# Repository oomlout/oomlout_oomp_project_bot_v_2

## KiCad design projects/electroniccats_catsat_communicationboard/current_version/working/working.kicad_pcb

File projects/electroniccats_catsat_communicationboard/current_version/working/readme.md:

# catsat
 
## summary 
* id: electroniccats_catsat_communicationboard
* user: electroniccats
* name: catsat
* board: communicationboard
* repo: https://github.com/ElectronicCats/CatSat
* src_file_repo_kicad_pcb: CommunicationBoard/CommunicationBoard.kicad_pcb
* src_file_repo_kicad_pcb_link: https://github.com/ElectronicCats/CatSat/tree/master/CommunicationBoard/CommunicationBoard.kicad_pcb

* src_file_repo_sch: CommunicationBoard/CommunicationBoard.sch
* src_file_repo_sch_link: https://github.com/ElectronicCats/CatSat/tree/master/CommunicationBoard/CommunicationBoard.sch
* full details link: https://github.com/oomlout/oomlout_oomp_project_bot_v_2/tree/main/projects/electroniccats_catsat_communicationboard/current_version/working

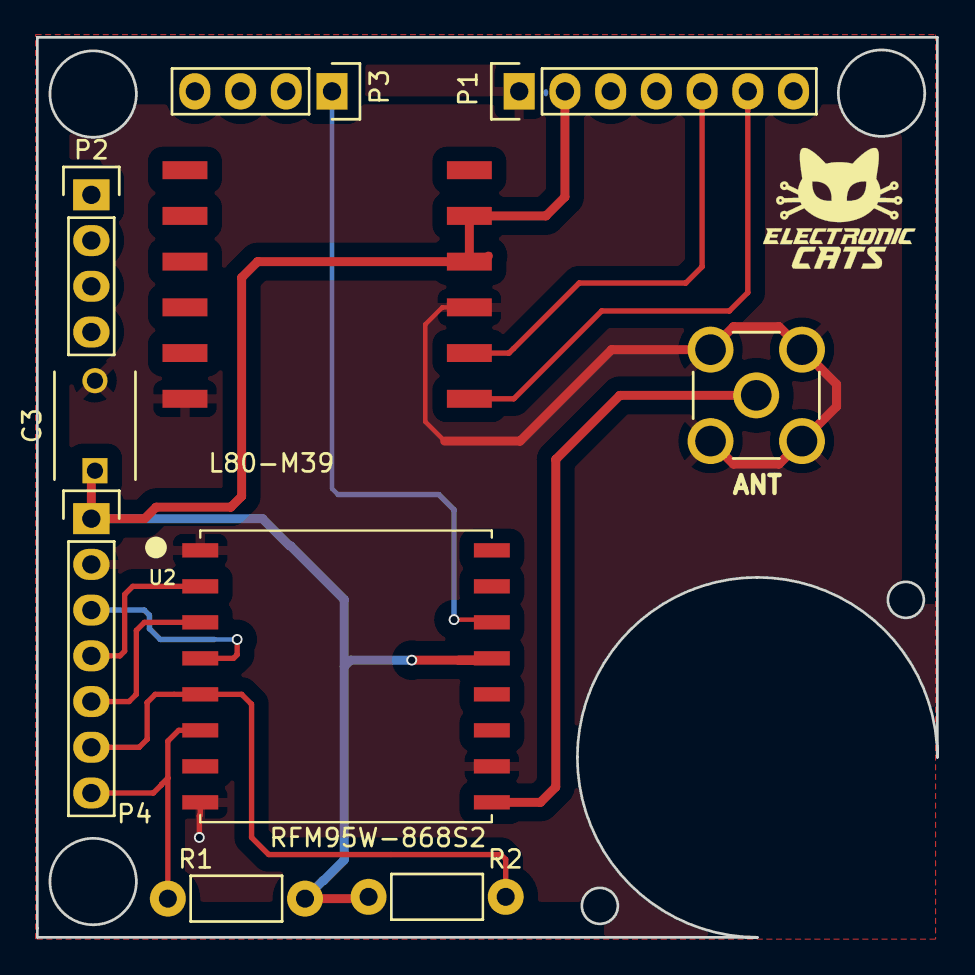
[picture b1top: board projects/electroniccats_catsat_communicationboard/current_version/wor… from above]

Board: 2 copper layers, 50.0 x 50.0 mm, 10 parts (0 on the bottom side), 11 nets.

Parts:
A1: ANT; AMPHENOL_901-144
C3: C; C_Disc_D6_P5
MODULE1: L80-M39; L80
P1, P4: CONN_01X07; Pin_Header_Straight_1x07
P2, P3: CONN_01X04; Pin_Header_Straight_1x04
R1, R2: R; Resistor_Horizontal_RM7mm
U2: RFM95W-868S2; RFM

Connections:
+BATT: C3.1, MODULE1.4, MODULE1.5, P1.2, P4.1, R1.1, R2.1, U2.13
GND: A1.2, A1.3, A1.4, A1.5, C3.2, MODULE1.3, MODULE1.12, P1.1, P4.2, U2.1, U2.8, U2.10
INT0: P3.1, U2.14
MISO: P4.4, U2.2
MOSI: P4.5, U2.3
NSS: P4.6, R2.2, U2.5
unnamed: A1.1, U2.9
RST: P4.7, R1.2, U2.6
SCK: P4.3, U2.4
S_RX: MODULE1.2, P1.5
S_TX: MODULE1.1, P1.6

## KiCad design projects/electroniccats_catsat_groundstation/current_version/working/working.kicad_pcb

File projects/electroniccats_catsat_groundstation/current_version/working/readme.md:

# catsat
 
## summary 
* id: electroniccats_catsat_groundstation
* user: electroniccats
* name: catsat
* board: groundstation
* repo: https://github.com/ElectronicCats/CatSat
* src_file_repo_kicad_pcb: GroundStation/GroundStation.kicad_pcb
* src_file_repo_kicad_pcb_link: https://github.com/ElectronicCats/CatSat/tree/master/GroundStation/GroundStation.kicad_pcb

* src_file_repo_sch: GroundStation/GroundStation.sch
* src_file_repo_sch_link: https://github.com/ElectronicCats/CatSat/tree/master/GroundStation/GroundStation.sch
* full details link: https://github.com/oomlout/oomlout_oomp_project_bot_v_2/tree/main/projects/electroniccats_catsat_groundstation/current_version/working

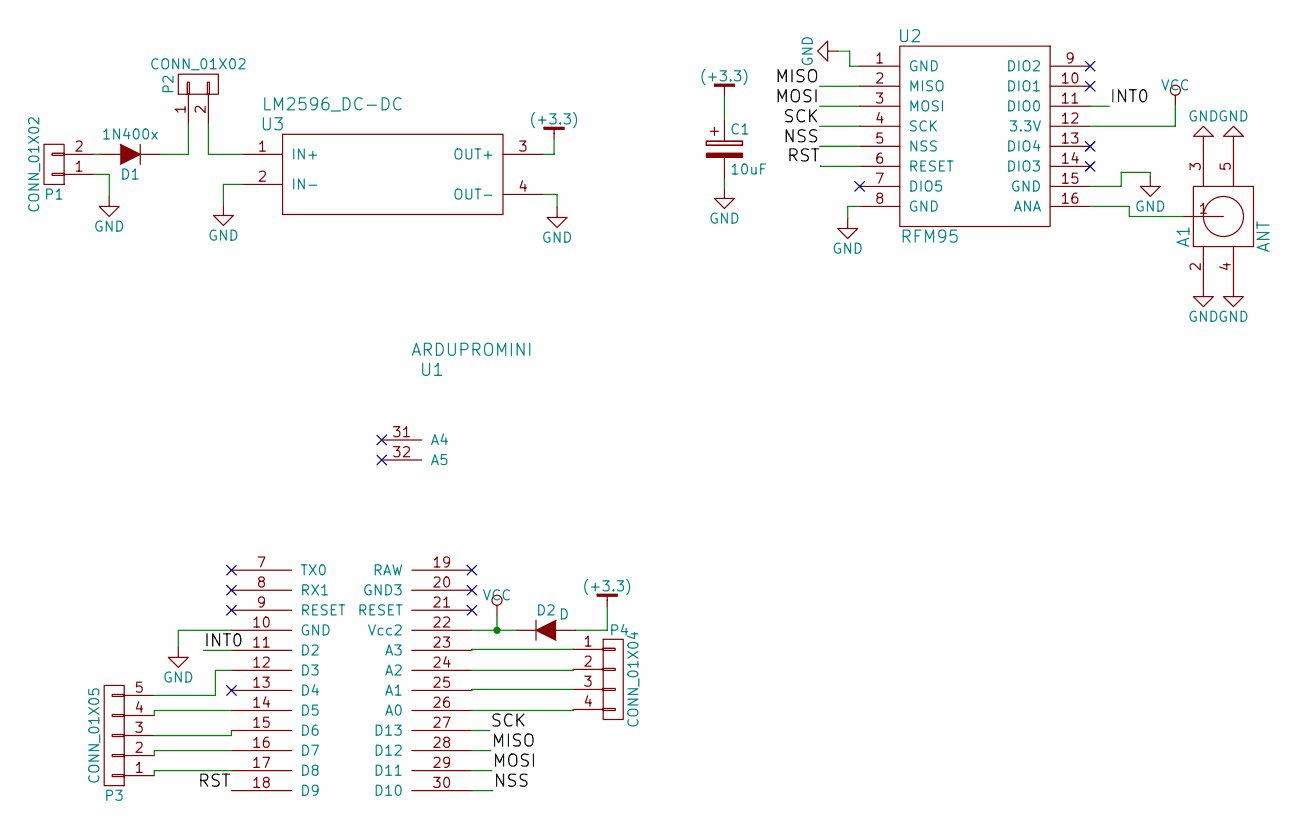
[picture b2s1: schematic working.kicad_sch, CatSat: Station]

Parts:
A1: ANT; AMPHENOL_901-144
C1: 10uF; C_Radial_D5_L6_P2.5
D1: 1N400x; Diode_DO-41_SOD81_Horizontal_RM10
D2: D; Diode_DO-41_SOD81_Horizontal_RM10
P1: CONN_01X02; bornier2
P2: CONN_01X02; Pin_Header_Straight_1x02
P3: CONN_01X05
P4: CONN_01X04
U1: ARDUPROMINI; arduinoMiniPro2
U2: RFM95; RFM
U3: LM2596_DC-DC; LM2596DC-DC

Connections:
(+3.3): C1.1, D2.2 (A), U3.3 (OUT+)
/INT0: U1.11 (D2), U2.11 (DIO0)
/MISO: U1.28 (D12), U2.2 (MISO)
/MOSI: U1.29 (D11), U2.3 (MOSI)
/NSS: U1.30 (D10), U2.5 (NSS)
/RST: U1.18 (D9), U2.6 (RESET)
/SCK: U1.27 (D13), U2.4 (SCK)
GND: A1.2, A1.3, A1.4, A1.5, C1.2, P1.1, U1.10 (GND), U2.1 (GND), U2.8 (GND), U2.15 (GND), U3.2 (IN-), U3.4 (OUT-)
unnamed: A1.1, U2.16 (ANA)
unnamed: D1.1 (K), P2.1
unnamed: D1.2 (A), P1.2
unnamed: P2.2, U3.1 (IN+)
unnamed: P3.1, U1.17 (D8)
unnamed: P3.2, U1.16 (D7)
unnamed: P3.3, U1.15 (D6)
unnamed: P3.4, U1.14 (D5)
unnamed: P3.5, U1.12 (D3)
unnamed: P4.1, U1.23 (A3)
unnamed: P4.2, U1.24 (A2)
unnamed: P4.3, U1.25 (A1)
unnamed: P4.4, U1.26 (A0)
VCC: D2.1 (K), U1.22 (Vcc2), U2.12 (3.3V)

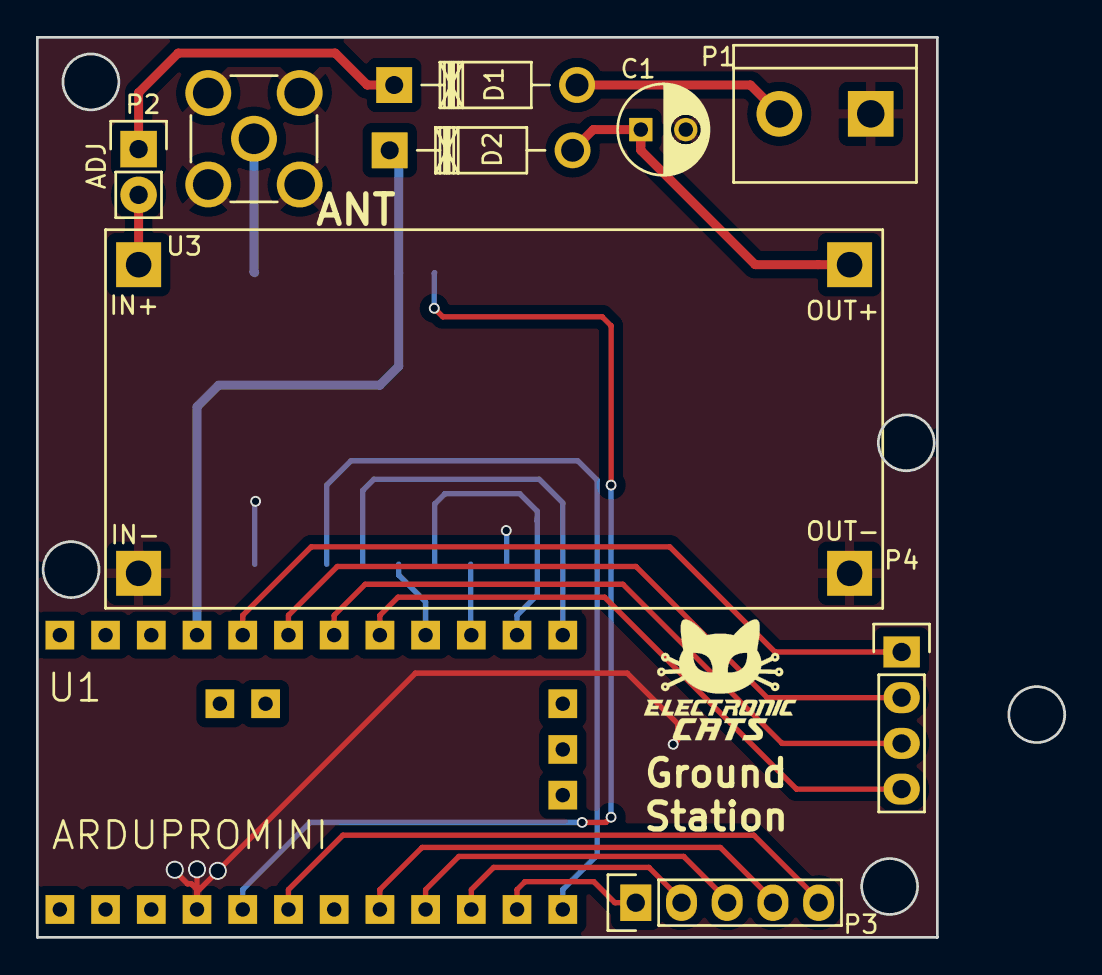
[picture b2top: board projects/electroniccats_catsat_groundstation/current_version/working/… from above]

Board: 2 copper layers, 50.0 x 50.0 mm, 11 parts (1 on the bottom side), 22 nets.

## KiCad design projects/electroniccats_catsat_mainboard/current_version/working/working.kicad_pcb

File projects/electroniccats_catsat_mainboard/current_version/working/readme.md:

# catsat
 
## summary 
* id: electroniccats_catsat_mainboard
* user: electroniccats
* name: catsat
* board: mainboard
* repo: https://github.com/ElectronicCats/CatSat
* src_file_repo_kicad_pcb: MainBoard/MainBoard.kicad_pcb
* src_file_repo_kicad_pcb_link: https://github.com/ElectronicCats/CatSat/tree/master/MainBoard/MainBoard.kicad_pcb

* src_file_repo_sch: MainBoard/MainBoard.sch
* src_file_repo_sch_link: https://github.com/ElectronicCats/CatSat/tree/master/MainBoard/MainBoard.sch
* full details link: https://github.com/oomlout/oomlout_oomp_project_bot_v_2/tree/main/projects/electroniccats_catsat_mainboard/current_version/working

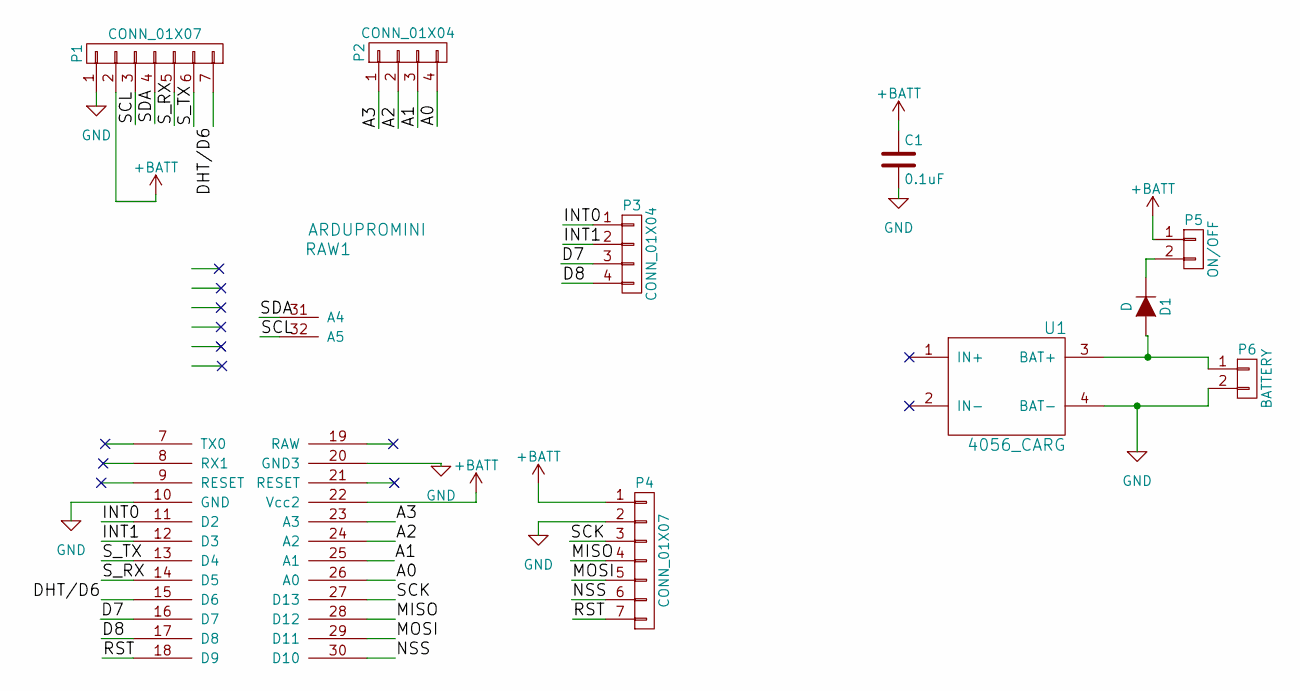
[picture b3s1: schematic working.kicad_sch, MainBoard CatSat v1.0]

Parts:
C1: 0.1uF; C_Disc_D6_P5
D1: D; Diode_DO-41_SOD81_Horizontal_RM10
P1, P4: CONN_01X07; Pin_Header_Straight_1x07
P2, P3: CONN_01X04; Pin_Header_Straight_1x04
P5: ON/OFF; Pin_Header_Angled_1x02
P6: BATTERY; Pin_Header_Straight_1x02
RAW1: ARDUPROMINI; arduinoMiniPro
U1: 4056_CARG; 4056_lipoCharg

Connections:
+BATT: C1.1, P1.2, P4.1, P5.1, RAW1.22 (Vcc2)
/A0: P2.4, RAW1.26 (A0)
/A1: P2.3, RAW1.25 (A1)
/A2: P2.2, RAW1.24 (A2)
/A3: P2.1, RAW1.23 (A3)
/D7: P3.3, RAW1.16 (D7)
/D8: P3.4, RAW1.17 (D8)
/DHT/D6: P1.7, RAW1.15 (D6)
/INT0: P3.1, RAW1.11 (D2)
/INT1: P3.2, RAW1.12 (D3)
/MISO: P4.4, RAW1.28 (D12)
/MOSI: P4.5, RAW1.29 (D11)
/NSS: P4.6, RAW1.30 (D10)
/RST: P4.7, RAW1.18 (D9)
/SCK: P4.3, RAW1.27 (D13)
/SCL: P1.3, RAW1.32 (A5)
/SDA: P1.4, RAW1.31 (A4)
/S_RX: P1.5, RAW1.14 (D5)
/S_TX: P1.6, RAW1.13 (D4)
GND: C1.2, P1.1, P4.2, P6.2, RAW1.10 (GND), RAW1.20 (GND3), U1.4 (BAT-)
unnamed: D1.1 (K), P5.2
unnamed: D1.2 (A), P6.1, U1.3 (BAT+)

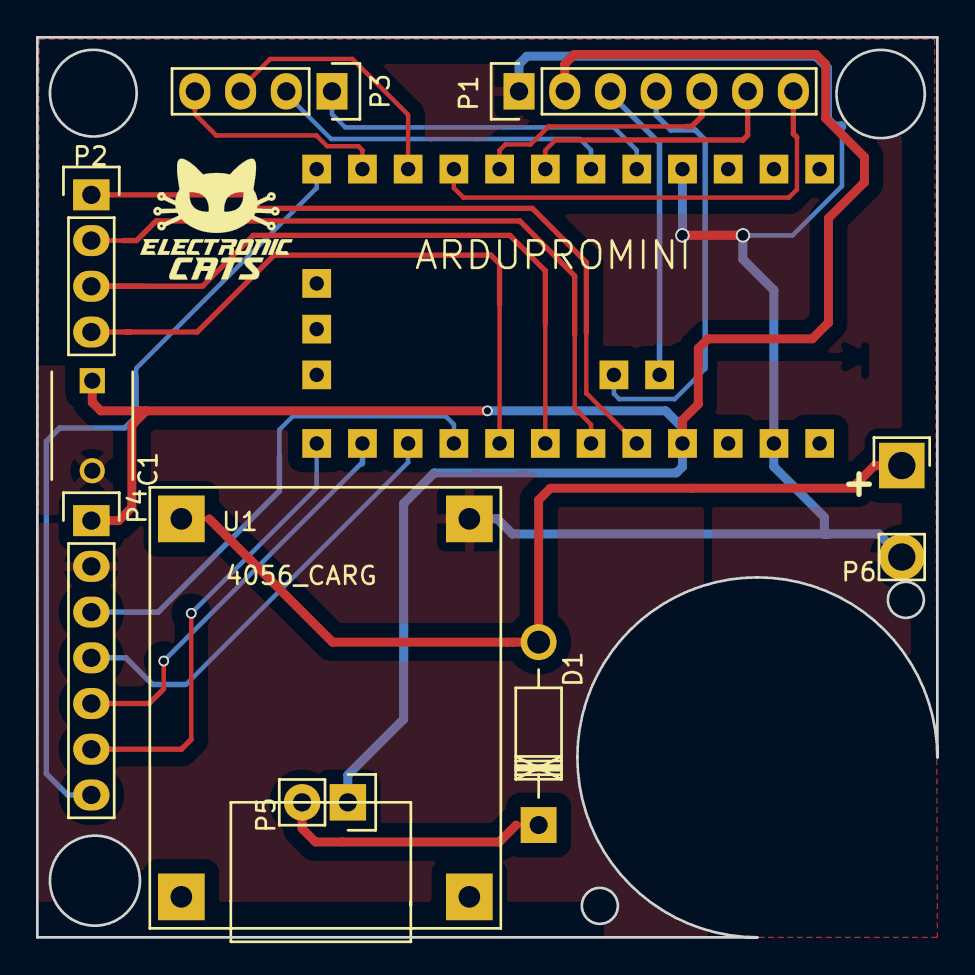
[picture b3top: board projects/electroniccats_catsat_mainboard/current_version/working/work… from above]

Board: 2 copper layers, 50.0 x 50.0 mm, 10 parts (0 on the bottom side), 22 nets.

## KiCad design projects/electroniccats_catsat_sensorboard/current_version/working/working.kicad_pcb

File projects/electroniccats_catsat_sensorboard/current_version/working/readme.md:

# catsat
 
## summary 
* id: electroniccats_catsat_sensorboard
* user: electroniccats
* name: catsat
* board: sensorboard
* repo: https://github.com/ElectronicCats/CatSat
* src_file_repo_kicad_pcb: SensorBoard/SensorBoard.kicad_pcb
* src_file_repo_kicad_pcb_link: https://github.com/ElectronicCats/CatSat/tree/master/SensorBoard/SensorBoard.kicad_pcb

* src_file_repo_sch: SensorBoard/SensorBoard.sch
* src_file_repo_sch_link: https://github.com/ElectronicCats/CatSat/tree/master/SensorBoard/SensorBoard.sch
* full details link: https://github.com/oomlout/oomlout_oomp_project_bot_v_2/tree/main/projects/electroniccats_catsat_sensorboard/current_version/working

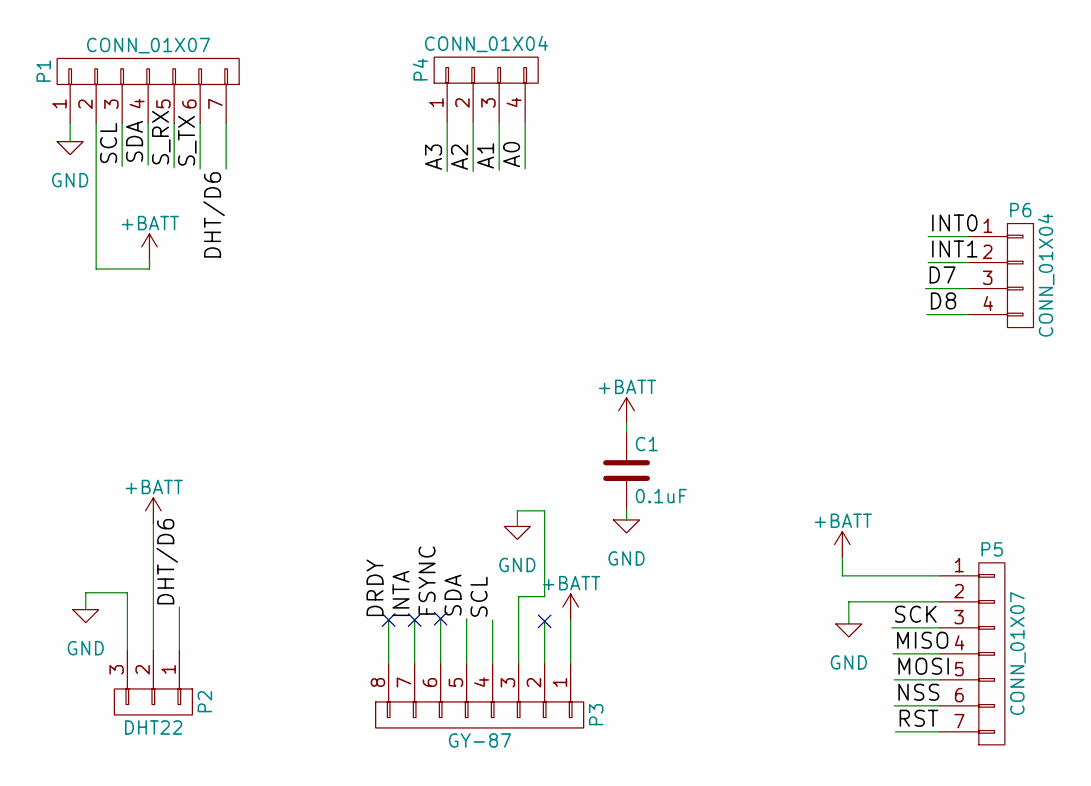
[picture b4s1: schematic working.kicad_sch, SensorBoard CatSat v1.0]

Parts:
C1: 0.1uF; C_Disc_D6_P5
P1, P5: CONN_01X07; Pin_Header_Straight_1x07
P2: DHT22; Pin_Header_Straight_1x03
P3: GY-87; Pin_Header_Straight_1x08
P4, P6: CONN_01X04; Pin_Header_Straight_1x04

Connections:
+BATT: C1.1, P1.2, P2.2, P3.1, P5.1
/A0: P4.4
/A1: P4.3
/A2: P4.2
/A3: P4.1
/D7: P6.3
/D8: P6.4
/DHT/D6: P1.7, P2.1
/DRDY: P3.8
/FSYNC: P3.6
/INT0: P6.1
/INT1: P6.2
/INTA: P3.7
/MISO: P5.4
/MOSI: P5.5
/NSS: P5.6
/RST: P5.7
/SCK: P5.3
/SCL: P1.3, P3.4
/SDA: P1.4, P3.5
/S_RX: P1.5
/S_TX: P1.6
GND: C1.2, P1.1, P2.3, P3.3, P5.2

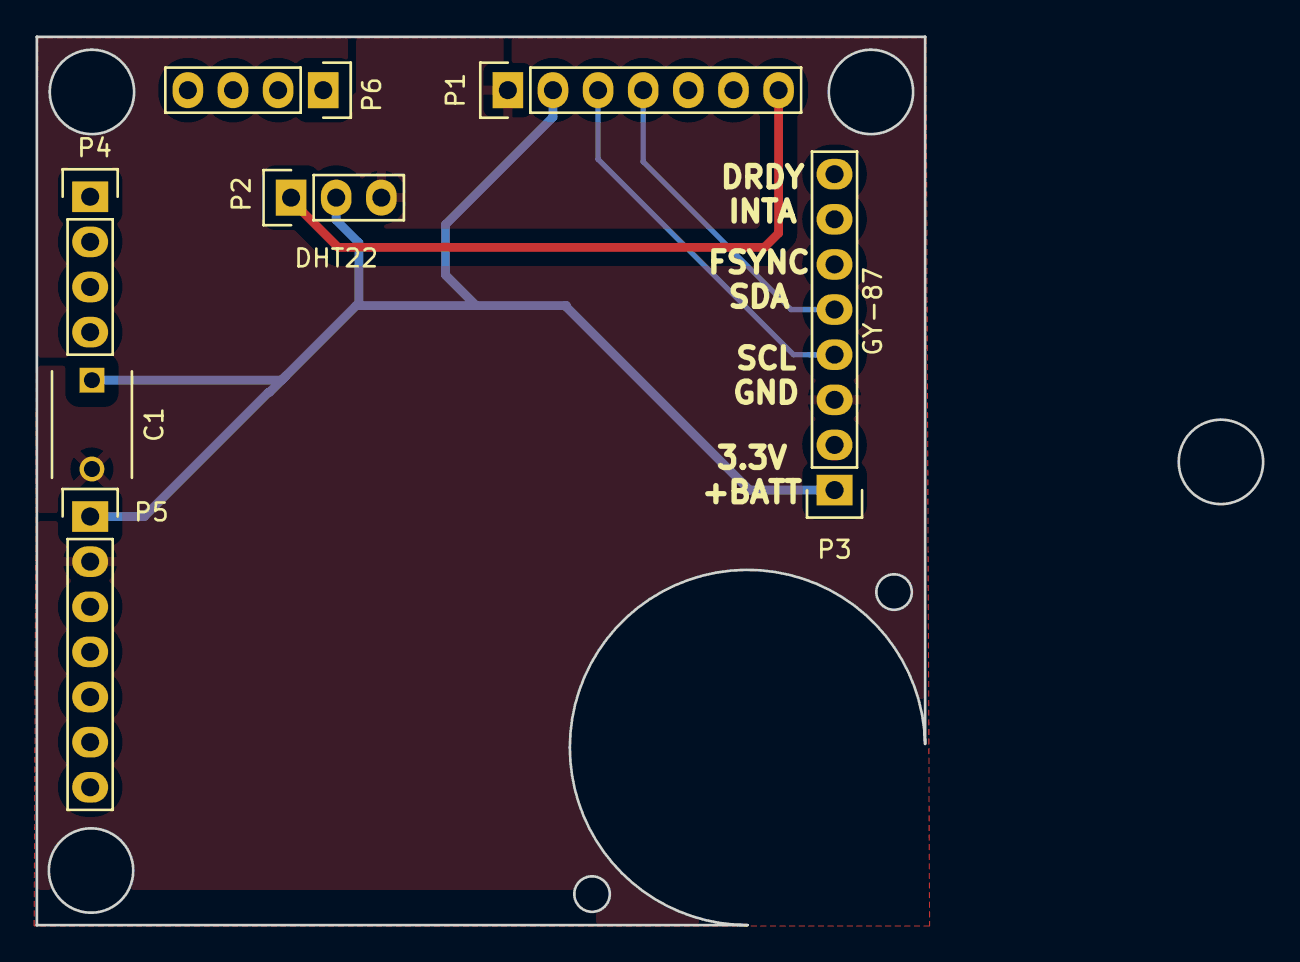
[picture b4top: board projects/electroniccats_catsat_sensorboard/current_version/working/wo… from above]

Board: 2 copper layers, 50.0 x 50.0 mm, 7 parts (0 on the bottom side), 5 nets.

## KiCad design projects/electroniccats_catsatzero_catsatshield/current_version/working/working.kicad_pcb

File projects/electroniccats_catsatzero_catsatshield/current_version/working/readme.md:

# catsatzero
 
## summary 
* id: electroniccats_catsatzero_catsatshield
* user: electroniccats
* name: catsatzero
* board: catsatshield
* repo: https://github.com/ElectronicCats/CatSatZero
* src_file_repo_kicad_pcb: CatSatShield/CaTSatShield.kicad_pcb
* src_file_repo_kicad_pcb_link: https://github.com/ElectronicCats/CatSatZero/tree/master/CatSatShield/CaTSatShield.kicad_pcb

* src_file_repo_sch: CatSatShield/CaTSatShield.sch
* src_file_repo_sch_link: https://github.com/ElectronicCats/CatSatZero/tree/master/CatSatShield/CaTSatShield.sch
* full details link: https://github.com/oomlout/oomlout_oomp_project_bot_v_2/tree/main/projects/electroniccats_catsatzero_catsatshield/current_version/working

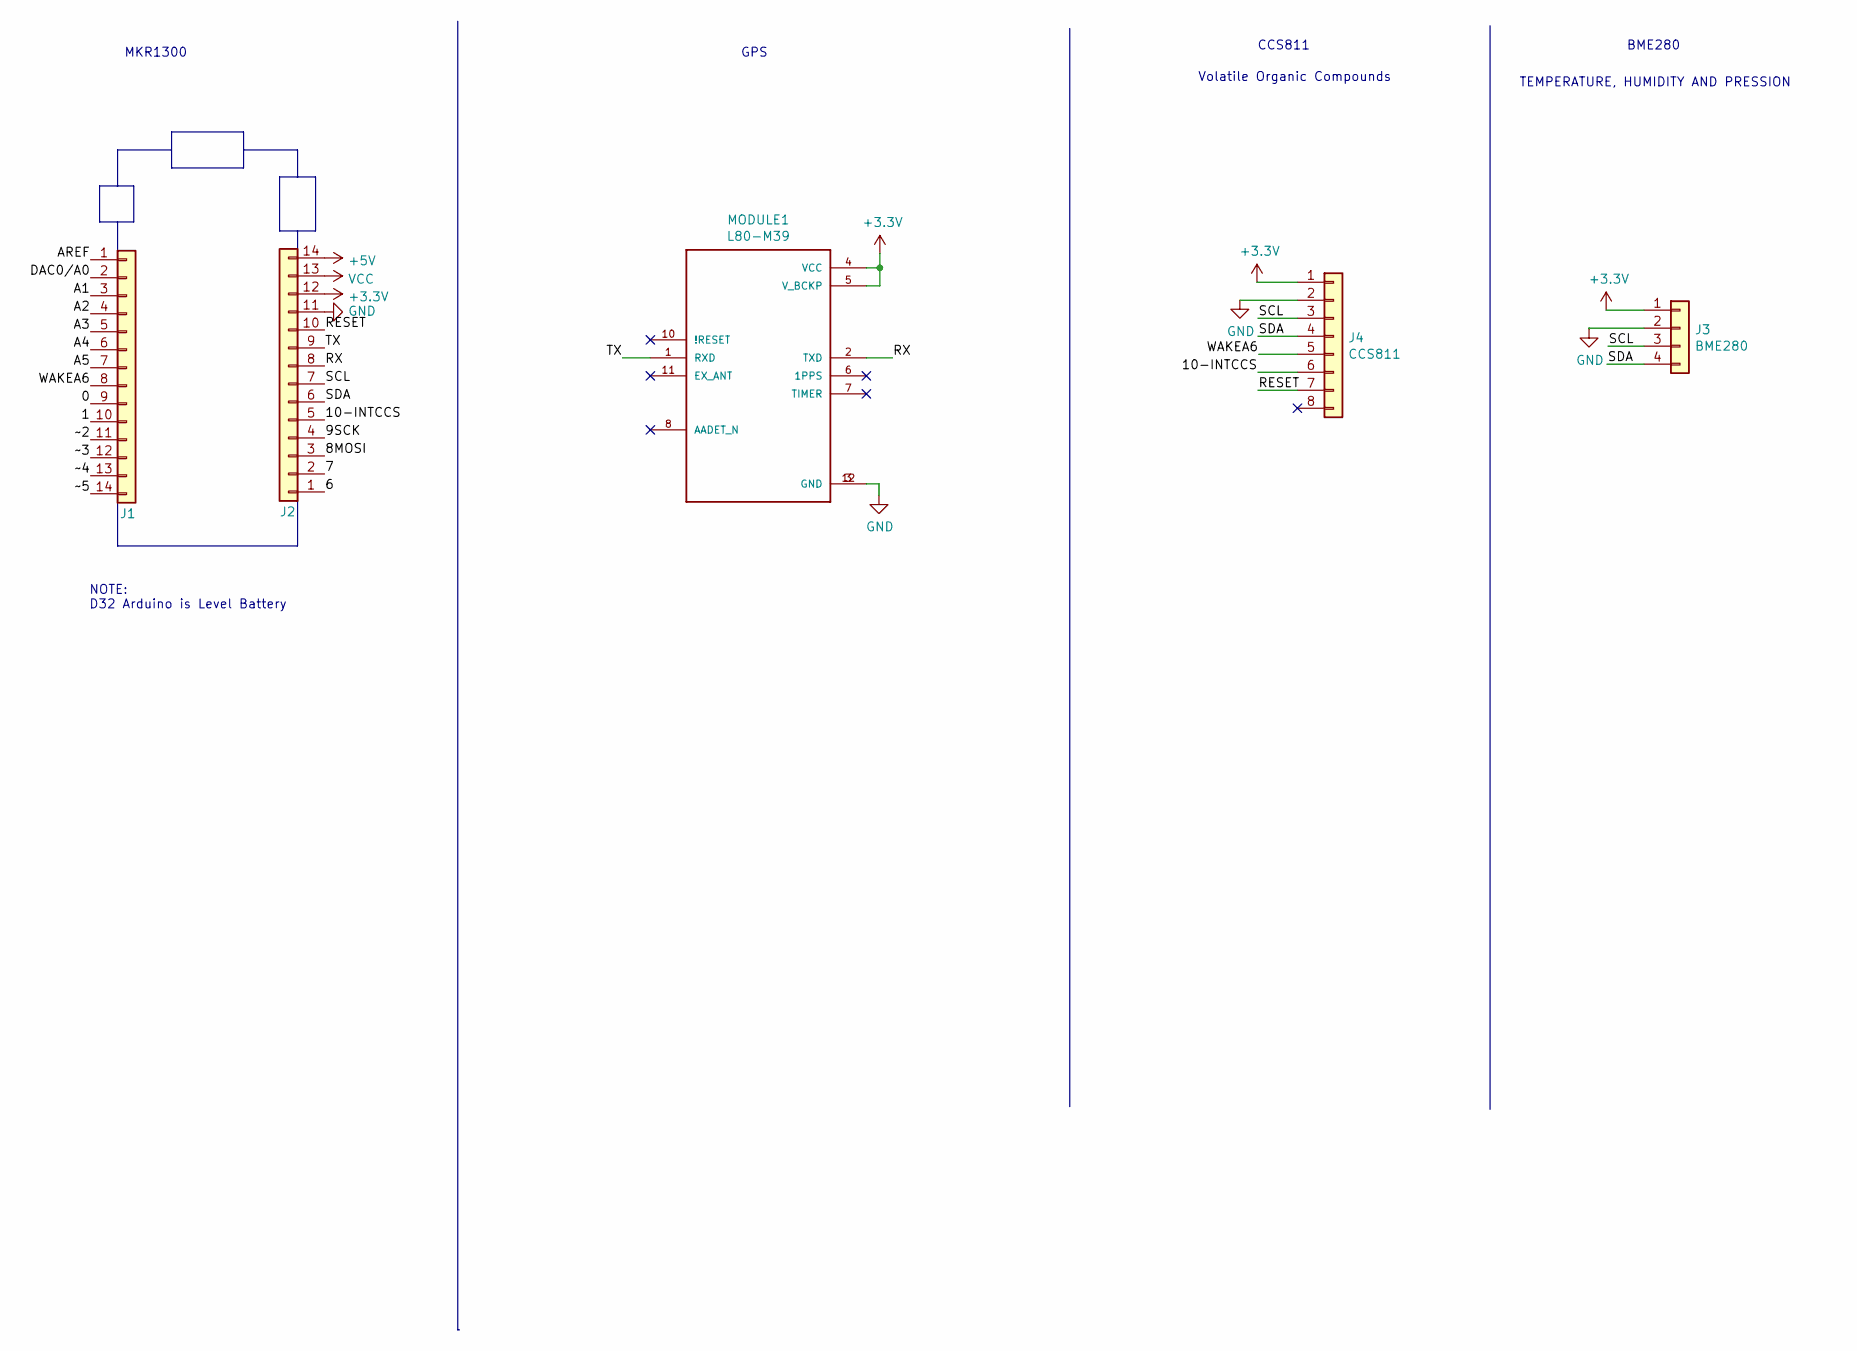
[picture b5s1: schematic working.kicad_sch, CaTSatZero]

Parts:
J1, J2: 61301411121
J3: BME280; PinSocket_1x04_P2.54mm_Vertical
J4: CCS811; Pin_Header_Straight_1x07_Pitch2.54mm
MODULE1: L80-M39; QUECTEL_L80-M39

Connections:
+3V3: J2.12, J3.1, J4.1, MODULE1.4 (VCC), MODULE1.5 (V_BCKP)
+5V: J2.14
/0: J1.9
/1: J1.10
/6: J2.1
/7: J2.2
/8MOSI: J2.3
/9SCK: J2.4
/10-INTCCS: J2.5, J4.6
/A1: J1.3
/A2: J1.4
/A3: J1.5
/A4: J1.6
/A5: J1.7
/AREF: J1.1
/DAC0/A0: J1.2
/RESET: J2.10, J4.7
/RX: J2.8, MODULE1.2 (TXD)
/SCL: J2.7, J3.3, J4.3
/SDA: J2.6, J3.4, J4.4
/TX: J2.9, MODULE1.1 (RXD)
/WAKEA6: J1.8, J4.5
/~2: J1.11
/~3: J1.12
/~4: J1.13
/~5: J1.14
GND: J2.11, J3.2, J4.2, MODULE1.3 (GND), MODULE1.12 (GND)
VCC: J2.13

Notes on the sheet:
TEMPERATURE, HUMIDITY AND PRESSION
Volatile Organic Compounds
NOTE: D32 Arduino is Level Battery
BME280
GPS
CCS811
MKR1300

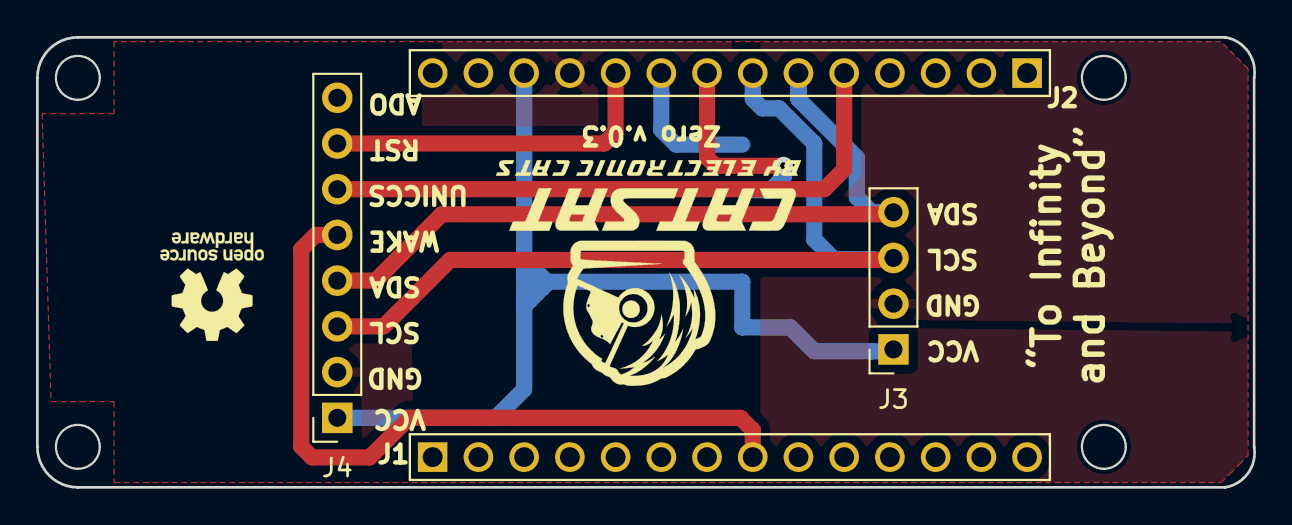
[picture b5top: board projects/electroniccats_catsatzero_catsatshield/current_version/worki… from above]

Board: 2 copper layers, 67.6 x 25.0 mm, 14 parts (1 on the bottom side), 9 nets.

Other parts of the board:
@HOLE0, @HOLE1, @HOLE2, @HOLE3: (no value)
FRAME1: Page 1; FRAME
U$5, U$6, U$7, U$8: MH_RND_F_2.2MM_NM

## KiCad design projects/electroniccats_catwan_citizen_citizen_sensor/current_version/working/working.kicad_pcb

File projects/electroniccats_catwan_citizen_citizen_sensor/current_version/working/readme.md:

# catwan_citizen
 
## summary 
* id: electroniccats_catwan_citizen_citizen_sensor
* user: electroniccats
* name: catwan_citizen
* board: citizen_sensor
* repo: https://github.com/ElectronicCats/CatWAN_Citizen
* src_file_repo_kicad_pcb: Hardware/citizen_sensor.kicad_pcb
* src_file_repo_kicad_pcb_link: https://github.com/ElectronicCats/CatWAN_Citizen/tree/master/Hardware/citizen_sensor.kicad_pcb
* src_file_repo_kicad_sch: Hardware/citizen_sensor.kicad_sch
* src_file_repo_kicad_sch_link: https://github.com/ElectronicCats/CatWAN_Citizen/tree/master/Hardware/citizen_sensor.kicad_sch

* src_file_repo_sch: Hardware/citizen_sensor.sch
* src_file_repo_sch_link: https://github.com/ElectronicCats/CatWAN_Citizen/tree/master/Hardware/citizen_sensor.sch
* full details link: https://github.com/oomlout/oomlout_oomp_project_bot_v_2/tree/main/projects/electroniccats_catwan_citizen_citizen_sensor/current_version/working

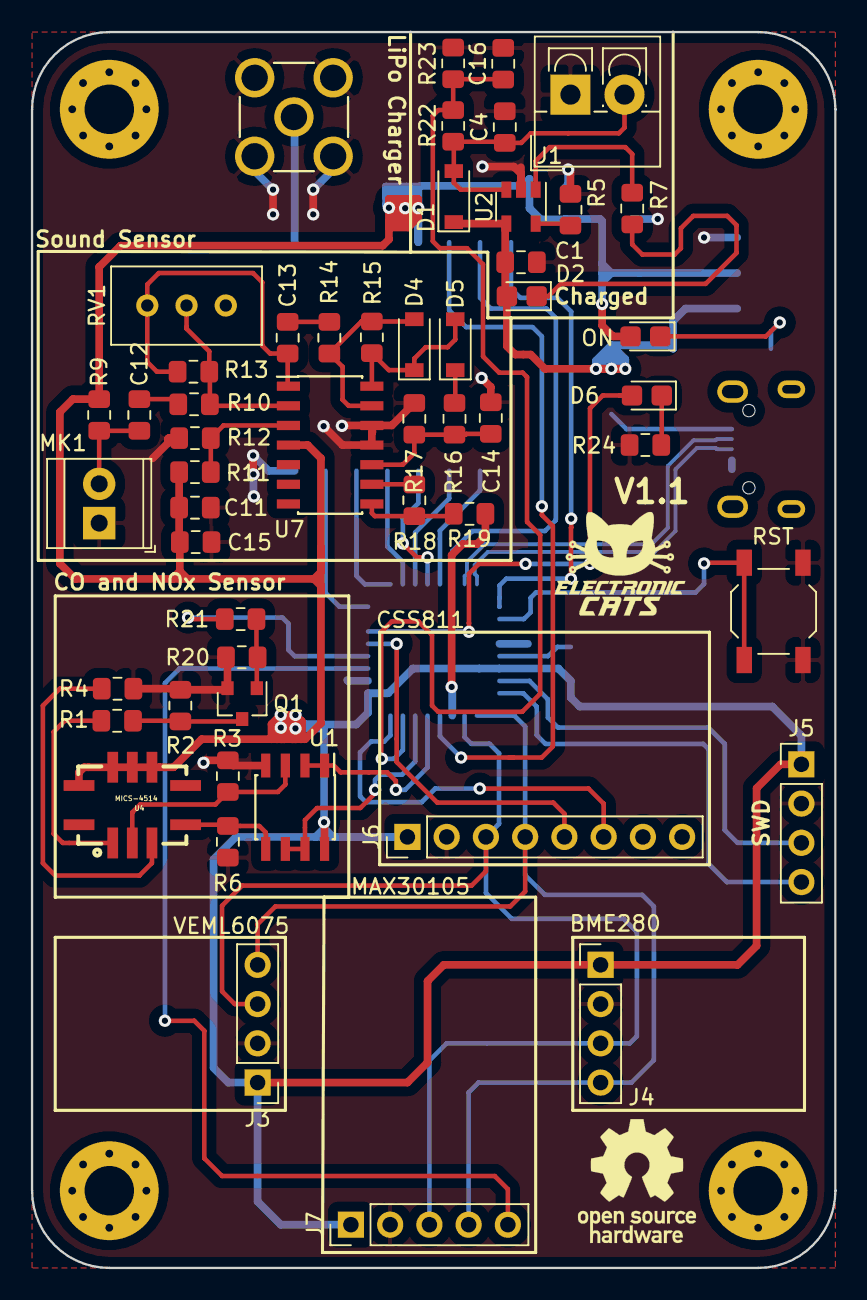
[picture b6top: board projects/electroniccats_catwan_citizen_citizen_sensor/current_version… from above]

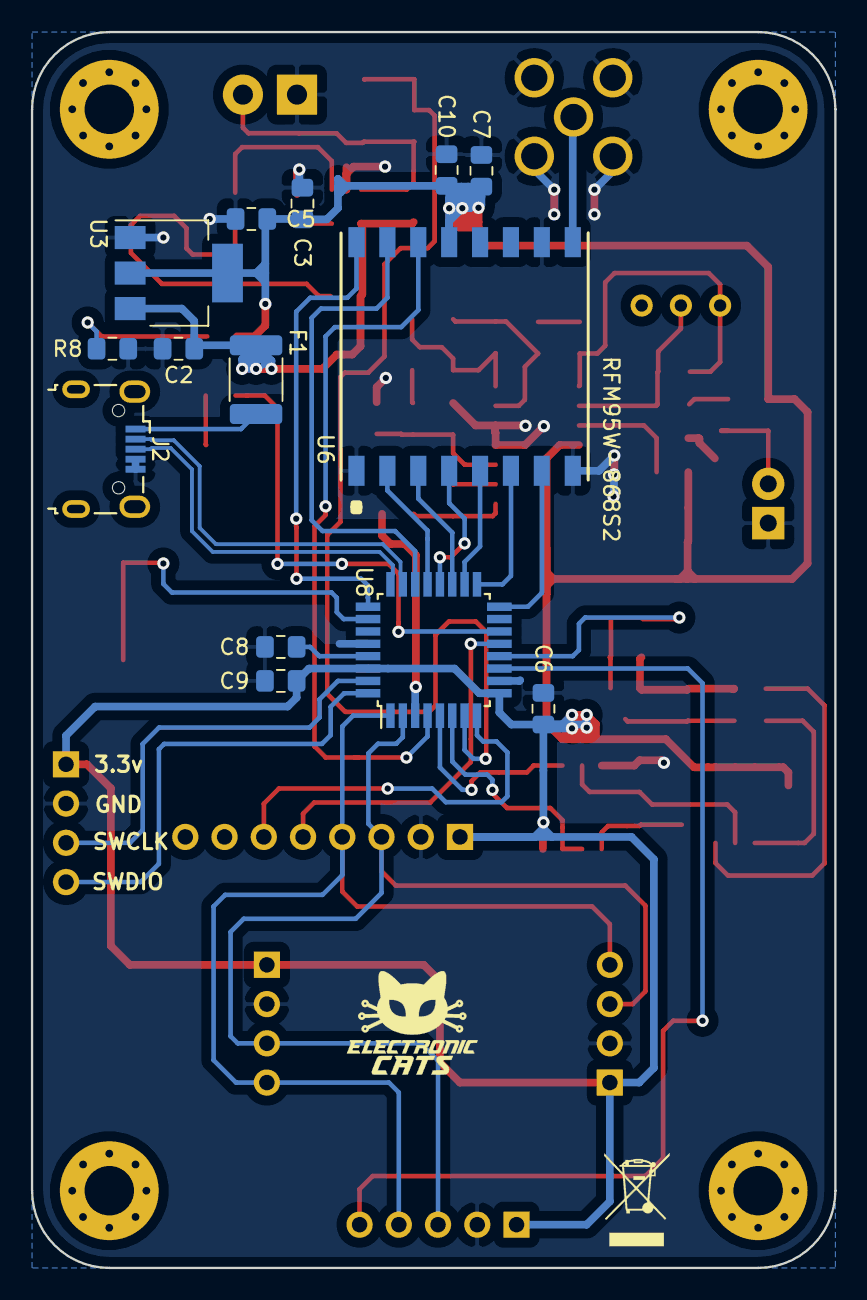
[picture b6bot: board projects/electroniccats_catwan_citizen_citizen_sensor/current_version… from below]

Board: 2 copper layers, 52.0 x 80.0 mm, 66 parts (14 on the bottom side), 55 nets.

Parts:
AE1: Antenna_Shield; AMPHENOL_901-144
C1, C2, C4, C5: 10uf; C_0805_2012Metric_Pad1.15x1.40mm_HandSolder
C3, C6, C7, C9, C15, C16: 0.1uf; C_0805_2012Metric_Pad1.15x1.40mm_HandSolder
C8, C10, C11: 1uf; C_0805_2012Metric_Pad1.15x1.40mm_HandSolder
C12, C14: 10uF; C_0805_2012Metric_Pad1.15x1.40mm_HandSolder
C13: 1uF; C_0805_2012Metric_Pad1.15x1.40mm_HandSolder
D1: D_Schottky; D_SOD-123
D2: CHARGE; LED_0805_2012Metric_Castellated
D3: ON; LED_0805_2012Metric_Castellated
D4, D5: RB751S40T1G; D_SOD-123
D6: Builtin; LED_0805_2012Metric_Castellated
F1: Fuse; Fuse_1812_4532Metric_Pad1.30x3.40mm_HandSolder
J1: BATT; TerminalBlock_4Ucon_1x02_P3.50mm_Vertical
J2: USB_B_Micro; USB_Micro-B_Wuerth_629105150521
J3: VEML6075; PinHeader_1x04_P2.54mm_Vertical
J4: BME280; PinHeader_1x04_P2.54mm_Vertical
J5: PROG; PinHeader_1x04_P2.54mm_Vertical
J6: CSS811; PinHeader_1x08_P2.54mm_Vertical
J7: MAX30105; PinHeader_1x05_P2.54mm_Vertical
MK1: Microphone; TerminalBlock_TE_282834-2_1x02_P2.54mm_Horizontal
Q1: 2N7002; SOT-23
R1, R4: 30; R_0805_2012Metric_Pad1.15x1.40mm_HandSolder
R2: 36; R_0805_2012Metric_Pad1.15x1.40mm_HandSolder
R3: 269; R_0805_2012Metric_Pad1.15x1.40mm_HandSolder
R5: 10k; R_0805_2012Metric_Pad1.15x1.40mm_HandSolder
R6: 47k; R_0805_2012Metric_Pad1.15x1.40mm_HandSolder
R7: 1k; R_0805_2012Metric_Pad1.15x1.40mm_HandSolder
R8, R24: 330; R_0805_2012Metric_Pad1.15x1.40mm_HandSolder
R9: 2.2K; R_0805_2012Metric_Pad1.15x1.40mm_HandSolder
R10, R18: 1K; R_0805_2012Metric_Pad1.15x1.40mm_HandSolder
R11, R12, R14, R17: 10K; R_0805_2012Metric_Pad1.15x1.40mm_HandSolder
R13: 100K; R_0805_2012Metric_Pad1.15x1.40mm_HandSolder
R15: 22K; R_0805_2012Metric_Pad1.15x1.40mm_HandSolder
R16, R19: 100; R_0805_2012Metric_Pad1.15x1.40mm_HandSolder
R20: 66.5k; R_0805_2012Metric_Pad1.15x1.40mm_HandSolder
R21: 66.5; R_0805_2012Metric_Pad1.15x1.40mm_HandSolder
R22: 680k; R_0805_2012Metric_Pad1.15x1.40mm_HandSolder
R23: 330k; R_0805_2012Metric_Pad1.15x1.40mm_HandSolder
RV1: 100K GAIN; Potentiometer_Bourns_3296W_Vertical
SW1: RST; SW_SPST_TL3342
U1: TLC2272; SOIC-8_3.9x4.9mm_P1.27mm
U2: MCP73831; SOT-23-5
U3: AP2114; SOT-223-3_TabPin2
U4: MICS-4514; MICS_10-SMD
U6: RFM95W-868S2; RFM95W
U7: LM324; SOIC-14_3.9x8.7mm_P1.27mm
U8: ATSAMD21E18A-MU; TQFP-32_7x7mm_P0.8mm

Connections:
+3V3: C3.1, C5.1, C6.1, C7.1, C9.1, C10.1, C11.1, C15.1, D3.2, J3.1, J4.1, J5.1, J6.1, J7.1, R9.1, R11.1, U1.8, U3.2, U4.F, U4.G, U4.H, U4.J, U6.13, U7.4, U8.9, U8.30
/ADC_OX: U1.1, U1.2, U8.5
/ADC_RED: U1.6, U1.7, U8.6
/BATT: C4.1, D1.2, J1.2, R22.2, U2.3
/BATTLEVEL: C16.1, R22.1, R23.2, U8.7
/CO2: R6.1, U1.5, U4.D
/D+: J2.3, U8.24
/D-: J2.2, U8.23
/DIO0: U6.14, U8.4
/DIO1: U6.15, U8.22
/DIO2: U6.16, U8.25
/DIO5: U6.7, U8.16
/ENVOL: R19.2, U8.3
/INT: J7.5, U8.11
/INTCSS: J6.6, U8.8
/LED_BUILTIN: D6.2, U8.14
/MISO: U6.2, U8.21
/MOSI: U6.3, U8.19
/NO2: R3.1, U1.3, U4.B
/PRE_HEALTING: R21.1, U8.12
/RFM_RST: U6.6, U8.17
/SCK: U6.4, U8.20
/SCL: J3.3, J4.3, J6.3, J7.3, U8.2
/SDA: J3.4, J4.4, J6.4, J7.4, U8.1
/SS: U6.5, U8.18
/SWCLK: J5.3, U8.31
/SWDIO: J5.4, U8.32
/WAKE: J6.5, U8.13
GND: AE1.2, C1.2, C2.2, C3.2, C4.2, C5.2, C6.2, C7.2, C8.2, C9.2, C10.2, C11.2, C14.1, C15.2, C16.2, J1.1, J2.4, J2.5, J3.2, J4.2, J5.2, J6.2, J7.2, MK1.1, Q1.2, R2.2, R3.2, R4.2, R5.2, R6.2, R8.2, R12.1, R17.1, R20.1, R23.1, R24.2, SW1.1, U1.4, U2.2, U3.1, U6.1, U6.8, U6.10, U7.11, U7.12, U8.10, U8.28
unnamed: AE1.1, U6.9
unnamed: C8.1, U8.29
unnamed: C12.1, MK1.2, R9.2
unnamed: C12.2, R10.2
unnamed: C13.1, R13.2, RV1.3, U7.1
unnamed: C13.2, R14.2
unnamed: C14.2, R16.1, R17.2, U7.10
unnamed: D2.1, R7.2
unnamed: D3.1, R8.1
unnamed: D4.1, D5.2, R15.1, U7.14
unnamed: D4.2, R14.1, R15.2, U7.13
unnamed: D5.1, R16.2
unnamed: D6.1, R24.1
unnamed: F1.1, J2.1
unnamed: Q1.1, R20.2, R21.2
unnamed: Q1.3, R1.2, R2.1
unnamed: R1.1, U4.A
unnamed: R4.1, U4.C
unnamed: R5.1, U2.5
unnamed: R7.1, U2.1
unnamed: R10.1, R13.1, RV1.2, U7.2
unnamed: R11.2, R12.2, U7.3
unnamed: R18.1, U7.9
unnamed: R18.2, R19.1, U7.8
unnamed: SW1.2, U8.26
VCC: C1.1, C2.1, D1.1, D2.2, F1.2, U2.4, U3.3
